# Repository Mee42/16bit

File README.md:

# [Dev notes](https://mee42.notion.site/mee42/16-bit-computer-63405d00fea146659e8c87a8048ab2e1)

8 bit sram wired to a 16 bit register and a 8 bit manual input:

snippet from the "schematic":

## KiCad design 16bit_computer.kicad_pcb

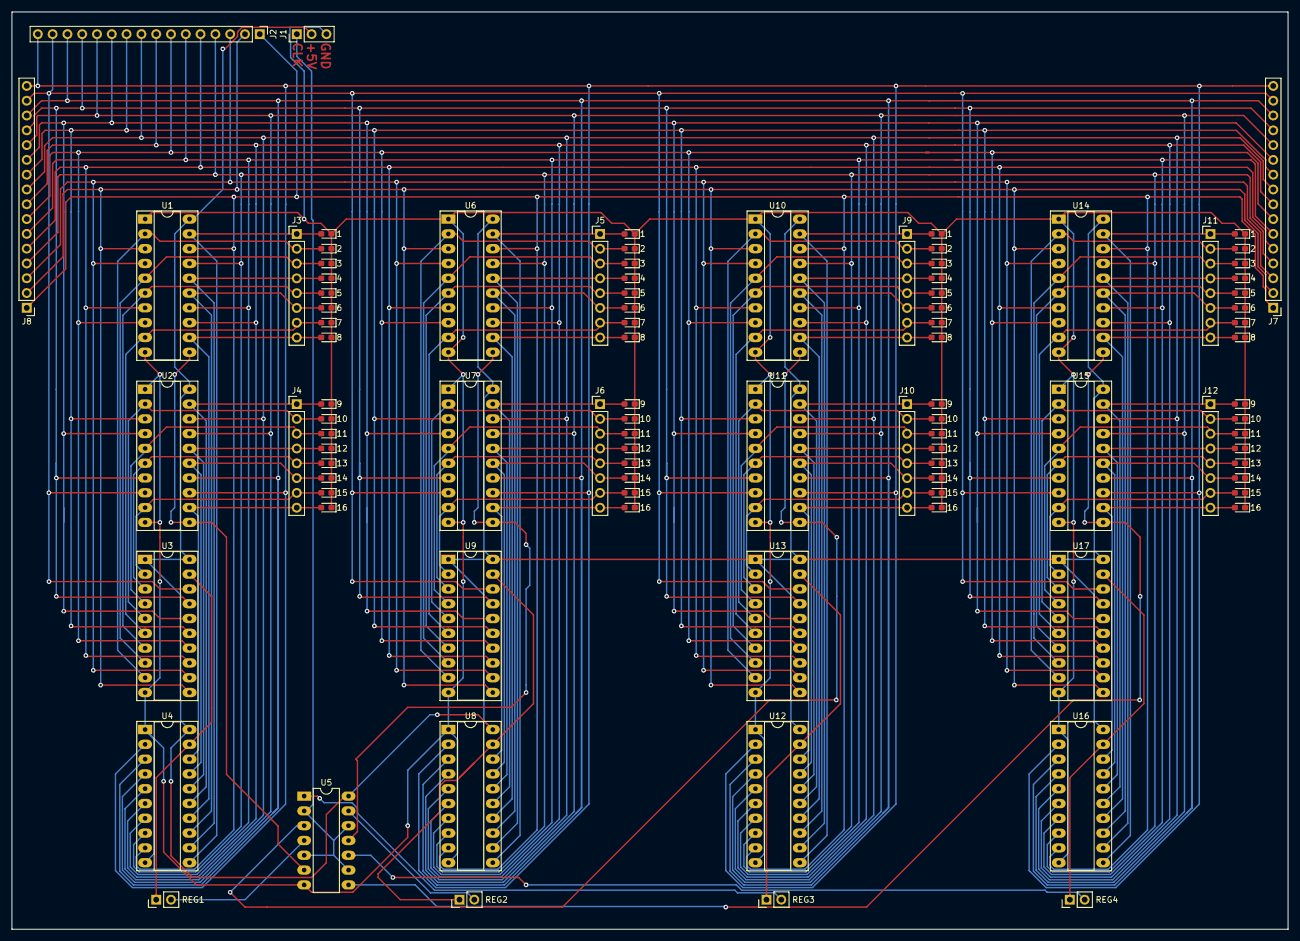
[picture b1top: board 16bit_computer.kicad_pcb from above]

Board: 2 copper layers, 219.1 x 157.5 mm, 97 parts (0 on the bottom side), 95 nets.

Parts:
D1, D2, D3, D4, D5, D6, D7, D8, D9, D10, D11, D12, D13, D14, D15, D16, D17, D18, D19, D20, D21, D22, D23, D24, D25, D26, D27, D28, D29, D30, D31, D32, D33, D34, D35, D36, D37, D38, D39, D40, D41, D42, D43, D44, D45, D46, D47, D48, D49, D50, D51, D52, D53, D54, D55, D56, D57, D58, D59, D60, D61, D62, D63, D64: LED; LED_0603_1608Metric_Pad1.05x0.95mm_HandSolder
J1: Conn_01x03; PinHeader_1x03_P2.54mm_Vertical
J2: Conn_01x16_Male; PinHeader_1x16_P2.54mm_Vertical
J3, J4, J5, J6, J9, J10, J11, J12: Conn_01x08; PinHeader_1x08_P2.54mm_Vertical
J7, J8: Conn_01x16; PinHeader_1x16_P2.54mm_Vertical
REG1, REG2, REG3, REG4: Conn_01x02; PinHeader_1x02_P2.54mm_Vertical
U1, U2, U6, U7, U10, U11, U14, U15: 40374; DIP-20_W7.62mm_Socket_LongPads
U3, U4, U8, U9, U12, U13, U16, U17: 40245; DIP-20_W7.62mm_Socket_LongPads
U5: 7408; DIP-14_W7.62mm_LongPads

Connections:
+5V: J1.2, U1.20 (Vdd), U2.20 (Vdd), U3.1 (Dir), U3.20 (Vdd), U4.20 (Vdd), U5.14, U6.20 (Vdd), U7.20 (Vdd), U8.20 (Vdd), U9.1 (Dir), U9.20 (Vdd), U10.20 (Vdd), U11.20 (Vdd), U12.20 (Vdd), U13.1 (Dir), U13.20 (Vdd), U14.20 (Vdd), U15.20 (Vdd), U16.20 (Vdd), U17.1 (Dir), U17.20 (Vdd)
/BUS1: J2.1, J7.1, J8.1, U1.18, U4.9, U6.18, U8.9, U10.18, U12.9, U14.18, U16.9
/BUS2: J2.2, J7.2, J8.2, U1.3, U3.11, U6.3, U9.11, U10.3, U13.11, U14.3, U17.11
/BUS3: J2.3, J7.3, J8.3, U1.4, U3.12, U6.4, U9.12, U10.4, U13.12, U14.4, U17.12
/BUS4: J2.4, J7.4, J8.4, U1.17, U4.8, U6.17, U8.8, U10.17, U12.8, U14.17, U16.8
/BUS5: J2.5, J7.5, J8.5, U1.7, U3.13, U6.7, U9.13, U10.7, U13.13, U14.7, U17.13
/BUS6: J2.6, J7.6, J8.6, U1.14, U4.7, U6.14, U8.7, U10.14, U12.7, U14.14, U16.7
/BUS7: J2.7, J7.7, J8.7, U1.8, U3.14, U6.8, U9.14, U10.8, U13.14, U14.8, U17.14
/BUS8: J2.8, J7.8, J8.8, U1.13, U4.6, U6.13, U8.6, U10.13, U12.6, U14.13, U16.6
/BUS9: J2.9, J7.9, J8.9, U2.18, U4.5, U7.18, U8.5, U11.18, U12.5, U15.18, U16.5
/BUS10: J2.10, J7.10, J8.10, U2.3, U3.15, U7.3, U9.15, U11.3, U13.15, U15.3, U17.15
/BUS11: J2.11, J7.11, J8.11, U2.4, U3.16, U7.4, U9.16, U11.4, U13.16, U15.4, U17.16
/BUS12: J2.12, J7.12, J8.12, U2.17, U4.4, U7.17, U8.4, U11.17, U12.4, U15.17, U16.4
/BUS13: J2.13, J7.13, J8.13, U2.7, U3.17, U7.7, U9.17, U11.7, U13.17, U15.7, U17.17
/BUS14: J2.14, J7.14, J8.14, U2.14, U4.3, U7.14, U8.3, U11.14, U12.3, U15.14, U16.3
/BUS15: J2.15, J7.15, J8.15, U2.8, U3.18, U7.8, U9.18, U11.8, U13.18, U15.8, U17.18
/BUS16: J2.16, J7.16, J8.16, U2.13, U4.2, U7.13, U8.2, U11.13, U12.2, U15.13, U16.2
/Register1/LOAD: U1.11 (Ck), U2.11 (Ck), U5.6
/Register1/data1: D1.2 (A), J3.1, U1.19, U4.11
/Register1/data2: D2.2 (A), J3.2, U1.2, U3.9
/Register1/data3: D3.2 (A), J3.3, U1.5, U3.8
/Register1/data4: D4.2 (A), J3.4, U1.16, U4.12
/Register1/data5: D5.2 (A), J3.5, U1.6, U3.7
/Register1/data6: D6.2 (A), J3.6, U1.15, U4.13
/Register1/data7: D7.2 (A), J3.7, U1.9, U3.6
/Register1/data8: D8.2 (A), J3.8, U1.12, U4.14
/Register1/data9: D9.2 (A), J4.1, U2.19, U4.15
/Register1/data10: D10.2 (A), J4.2, U2.2, U3.5
/Register1/data11: D11.2 (A), J4.3, U2.5, U3.4
/Register1/data12: D12.2 (A), J4.4, U2.16, U4.16
/Register1/data13: D13.2 (A), J4.5, U2.6, U3.3
/Register1/data14: D14.2 (A), J4.6, U2.15, U4.17
/Register1/data15: D15.2 (A), J4.7, U2.9, U3.2
/Register1/data16: D16.2 (A), J4.8, U2.12, U4.18
/Register1/~ENABLE: REG1.1, U3.19 (~G), U4.19 (~G)
/Register2/LOAD: U5.11, U6.11 (Ck), U7.11 (Ck)
/Register2/data1: D17.2 (A), J5.1, U6.19, U8.11
/Register2/data2: D18.2 (A), J5.2, U6.2, U9.9
/Register2/data3: D19.2 (A), J5.3, U6.5, U9.8
/Register2/data4: D20.2 (A), J5.4, U6.16, U8.12
/Register2/data5: D21.2 (A), J5.5, U6.6, U9.7
/Register2/data6: D22.2 (A), J5.6, U6.15, U8.13
/Register2/data7: D23.2 (A), J5.7, U6.9, U9.6
/Register2/data8: D24.2 (A), J5.8, U6.12, U8.14
/Register2/data9: D25.2 (A), J6.1, U7.19, U8.15
/Register2/data10: D26.2 (A), J6.2, U7.2, U9.5
/Register2/data11: D27.2 (A), J6.3, U7.5, U9.4
/Register2/data12: D28.2 (A), J6.4, U7.16, U8.16
/Register2/data13: D29.2 (A), J6.5, U7.6, U9.3
/Register2/data14: D30.2 (A), J6.6, U7.15, U8.17
/Register2/data15: D31.2 (A), J6.7, U7.9, U9.2
/Register2/data16: D32.2 (A), J6.8, U7.12, U8.18
/Register2/~ENABLE: REG2.1, U8.19 (~G), U9.19 (~G)
/Register3/LOAD: U5.3, U10.11 (Ck), U11.11 (Ck)
/Register3/data1: D33.2 (A), J9.1, U10.19, U12.11
/Register3/data2: D34.2 (A), J9.2, U10.2, U13.9
/Register3/data3: D35.2 (A), J9.3, U10.5, U13.8
/Register3/data4: D36.2 (A), J9.4, U10.16, U12.12
/Register3/data5: D37.2 (A), J9.5, U10.6, U13.7
/Register3/data6: D38.2 (A), J9.6, U10.15, U12.13
/Register3/data7: D39.2 (A), J9.7, U10.9, U13.6
/Register3/data8: D40.2 (A), J9.8, U10.12, U12.14
/Register3/data9: D41.2 (A), J10.1, U11.19, U12.15
/Register3/data10: D42.2 (A), J10.2, U11.2, U13.5
/Register3/data11: D43.2 (A), J10.3, U11.5, U13.4
/Register3/data12: D44.2 (A), J10.4, U11.16, U12.16
/Register3/data13: D45.2 (A), J10.5, U11.6, U13.3
/Register3/data14: D46.2 (A), J10.6, U11.15, U12.17
/Register3/data15: D47.2 (A), J10.7, U11.9, U13.2
/Register3/data16: D48.2 (A), J10.8, U11.12, U12.18
/Register3/~ENABLE: REG3.1, U12.19 (~G), U13.19 (~G)
/Register4/LOAD: U5.8, U14.11 (Ck), U15.11 (Ck)
/Register4/data1: D49.2 (A), J11.1, U14.19, U16.11
/Register4/data2: D50.2 (A), J11.2, U14.2, U17.9
/Register4/data3: D51.2 (A), J11.3, U14.5, U17.8
/Register4/data4: D52.2 (A), J11.4, U14.16, U16.12
/Register4/data5: D53.2 (A), J11.5, U14.6, U17.7
/Register4/data6: D54.2 (A), J11.6, U14.15, U16.13
/Register4/data7: D55.2 (A), J11.7, U14.9, U17.6
/Register4/data8: D56.2 (A), J11.8, U14.12, U16.14
/Register4/data9: D57.2 (A), J12.1, U15.19, U16.15
/Register4/data10: D58.2 (A), J12.2, U15.2, U17.5
/Register4/data11: D59.2 (A), J12.3, U15.5, U17.4
/Register4/data12: D60.2 (A), J12.4, U15.16, U16.16
/Register4/data13: D61.2 (A), J12.5, U15.6, U17.3
/Register4/data14: D62.2 (A), J12.6, U15.15, U16.17
/Register4/data15: D63.2 (A), J12.7, U15.9, U17.2
/Register4/data16: D64.2 (A), J12.8, U15.12, U16.18
/Register4/~ENABLE: REG4.1, U16.19 (~G), U17.19 (~G)
CLK: J1.1, U5.2, U5.5, U5.9, U5.12
GND: D1.1 (K), D2.1 (K), D3.1 (K), D4.1 (K), D5.1 (K), D6.1 (K), D7.1 (K), D8.1 (K), D9.1 (K), D10.1 (K), D11.1 (K), D12.1 (K), D13.1 (K), D14.1 (K), D15.1 (K), D16.1 (K), D17.1 (K), D18.1 (K), D19.1 (K), D20.1 (K), D21.1 (K), D22.1 (K), D23.1 (K), D24.1 (K), D25.1 (K), D26.1 (K), D27.1 (K), D28.1 (K), D29.1 (K), D30.1 (K), D31.1 (K), D32.1 (K), D33.1 (K), D34.1 (K), D35.1 (K), D36.1 (K), D37.1 (K), D38.1 (K), D39.1 (K), D40.1 (K), D41.1 (K), D42.1 (K), D43.1 (K), D44.1 (K), D45.1 (K), D46.1 (K), D47.1 (K), D48.1 (K), D49.1 (K), D50.1 (K), D51.1 (K), D52.1 (K), D53.1 (K), D54.1 (K), D55.1 (K), D56.1 (K), D57.1 (K), D58.1 (K), D59.1 (K), D60.1 (K), D61.1 (K), D62.1 (K), D63.1 (K), D64.1 (K), J1.3, U1.1 (~E), U1.10 (Vss), U2.1 (~E), U2.10 (Vss), U3.10 (Vss), U4.1 (Dir), U4.10 (Vss), U5.7, U6.1 (~E), U6.10 (Vss), U7.1 (~E), U7.10 (Vss), U8.1 (Dir), U8.10 (Vss), U9.10 (Vss), U10.1 (~E), U10.10 (Vss), U11.1 (~E), U11.10 (Vss), U12.1 (Dir), U12.10 (Vss), U13.10 (Vss), U14.1 (~E), U14.10 (Vss), U15.1 (~E), U15.10 (Vss), U16.1 (Dir), U16.10 (Vss), U17.10 (Vss)
unnamed: REG1.2, U5.4
unnamed: REG2.2, U5.13
unnamed: REG3.2, U5.1
unnamed: REG4.2, U5.10

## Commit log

2022-10-28 good, checking code in to try and dup it now
2022-11-02 register finished?
2022-11-02 final v0.3
